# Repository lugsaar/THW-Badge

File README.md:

# THW-Badge

 [![CC BY-NC-SA 4.0][cc-by-nc-sa-shield]][cc-by-nc-sa]

## Images 

## License 

This work is licensed under a
[Creative Commons Attribution-NonCommercial-ShareAlike 4.0 International License][cc-by-nc-sa].

[![CC BY-NC-SA 4.0][cc-by-nc-sa-image]][cc-by-nc-sa]

[cc-by-nc-sa]: http://creativecommons.org/licenses/by-nc-sa/4.0/
[cc-by-nc-sa-image]: https://licensebuttons.net/l/by-nc-sa/4.0/88x31.png
[cc-by-nc-sa-shield]: https://img.shields.io/badge/License-CC%20BY--NC--SA%204.0-lightgrey.svg

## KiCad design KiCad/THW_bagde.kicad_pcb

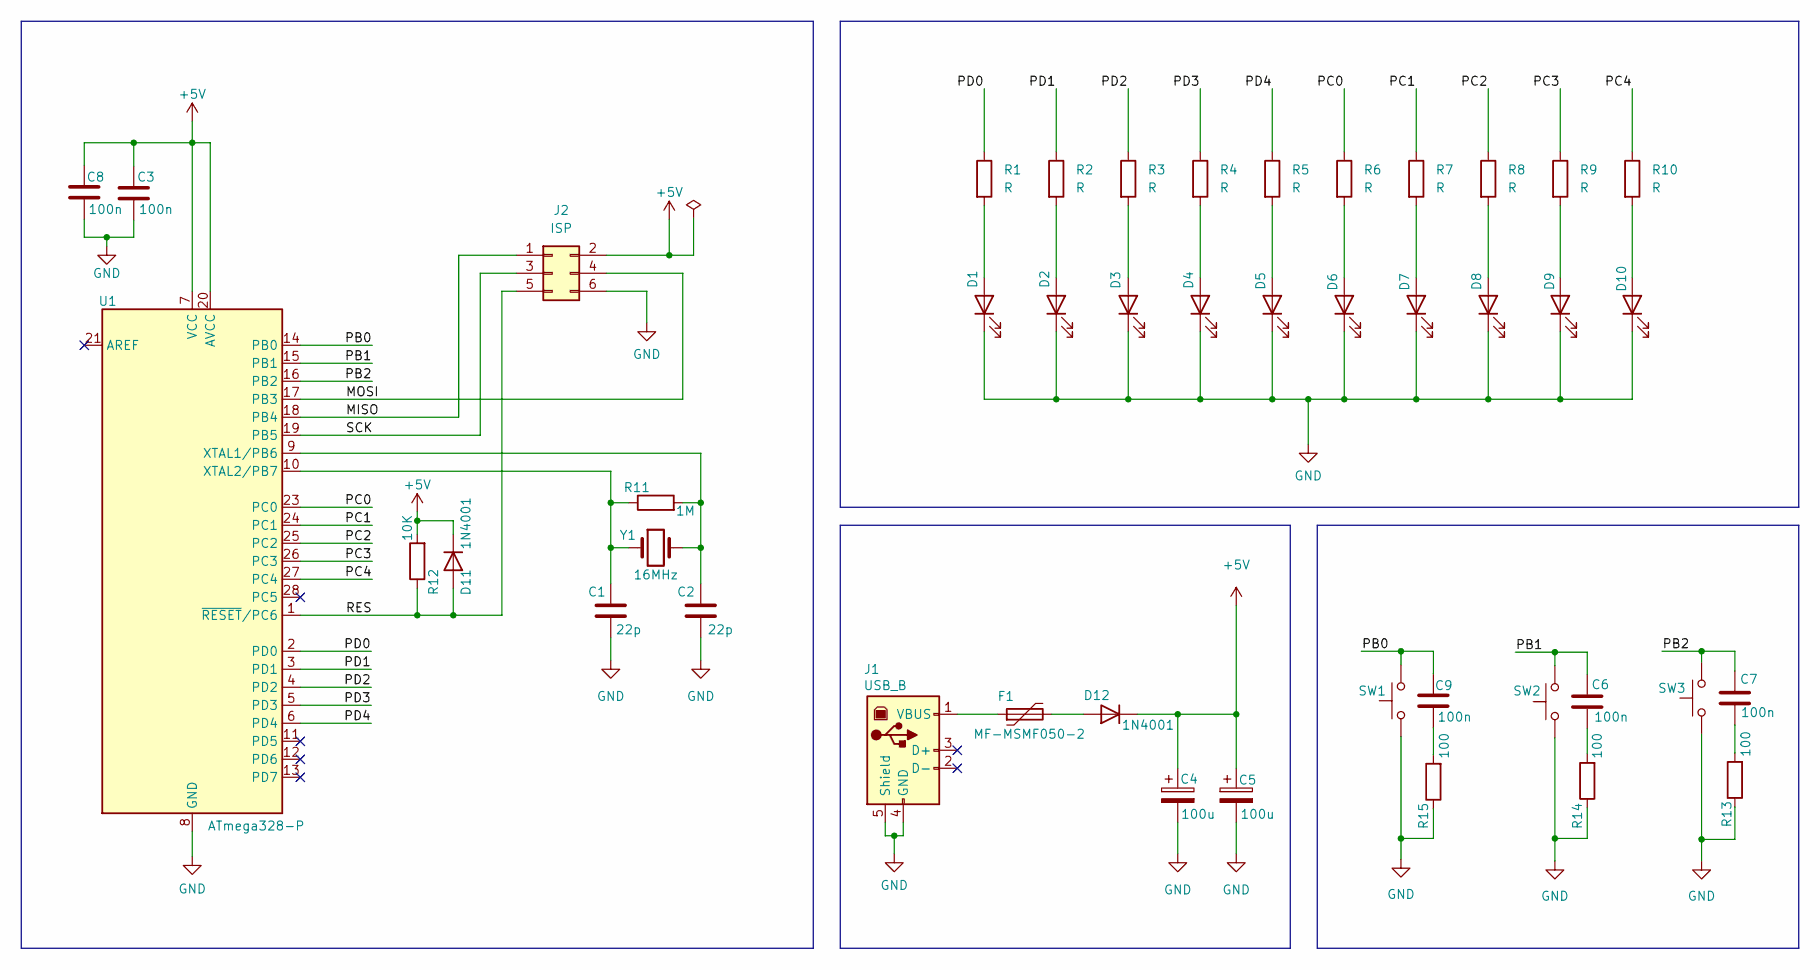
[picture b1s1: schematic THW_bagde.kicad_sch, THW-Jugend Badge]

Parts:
C1, C2: 22p; C_Disc_D3.8mm_W2.6mm_P2.50mm
C3, C6, C7, C8, C9: 100n; C_Disc_D3.8mm_W2.6mm_P2.50mm
C4, C5: 100u; CP_Radial_D6.3mm_P2.50mm
D1, D2, D3, D4, D5, D6, D7, D8, D9, D10: LED; LED_D3.0mm_Clear
D11, D12: 1N4001; D_DO-41_SOD81_P10.16mm_Horizontal
F1: MF-MSMF050-2; Fuse_1812_4532Metric
J1: USB_B; USB_B_Lumberg_2411_02_Horizontal
J2: ISP; PinHeader_2x03_P2.54mm_Vertical
R1, R2, R3, R4, R5, R6, R7, R8, R9, R10: R; R_Axial_DIN0207_L6.3mm_D2.5mm_P10.16mm_Horizontal
R11: 1M; R_Axial_DIN0207_L6.3mm_D2.5mm_P10.16mm_Horizontal
R12: 10K; R_Axial_DIN0207_L6.3mm_D2.5mm_P10.16mm_Horizontal
R13, R14, R15: 100; R_Axial_DIN0207_L6.3mm_D2.5mm_P10.16mm_Horizontal
SW1, SW2, SW3: SW_Push; SW_PUSH_6mm
U1: ATmega328-P; DIP-28_W7.62mm
Y1: 16MHz; Crystal_HC49-4H_Vertical

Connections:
+5V: C3.1, C4.1, C5.1, C8.1, D11.1 (K), D12.1 (K), J2.2, R12.2, U1.7 (VCC), U1.20 (AVCC)
/MISO: J2.1, U1.18 (PB4)
/MOSI: J2.4, U1.17 (PB3)
/PB0: C9.1, SW1.2, U1.14 (PB0)
/PB1: C6.1, SW2.2, U1.15 (PB1)
/PB2: C7.1, SW3.2, U1.16 (PB2)
/PC0: R6.1, U1.23 (PC0)
/PC1: R7.1, U1.24 (PC1)
/PC2: R8.1, U1.25 (PC2)
/PC3: R9.1, U1.26 (PC3)
/PC4: R10.1, U1.27 (PC4)
/PD0: R1.1, U1.2 (PD0)
/PD1: R2.1, U1.3 (PD1)
/PD2: R3.1, U1.4 (PD2)
/PD3: R4.1, U1.5 (PD3)
/PD4: R5.1, U1.6 (PD4)
/RES: D11.2 (A), J2.5, R12.1, U1.1 (~RESET/PC6)
/SCK: J2.3, U1.19 (PB5)
GND: C1.2, C2.2, C3.2, C4.2, C5.2, C8.2, D1.1 (K), D2.1 (K), D3.1 (K), D4.1 (K), D5.1 (K), D6.1 (K), D7.1 (K), D8.1 (K), D9.1 (K), D10.1 (K), J1.4 (GND), J1.5 (Shield), J2.6, R13.1, R14.1, R15.1, SW1.1, SW2.1, SW3.1, U1.8 (GND), U1.22 (GND)
unnamed: C1.1, R11.1, U1.10 (XTAL2/PB7), Y1.1
unnamed: C2.1, R11.2, U1.9 (XTAL1/PB6), Y1.2
unnamed: C7.2, R13.2
unnamed: C9.2, R15.2
unnamed: D1.2 (A), R1.2
unnamed: D2.2 (A), R2.2
unnamed: D3.2 (A), R3.2
unnamed: D4.2 (A), R4.2
unnamed: D5.2 (A), R5.2
unnamed: D6.2 (A), R6.2
unnamed: D7.2 (A), R7.2
unnamed: D8.2 (A), R8.2
unnamed: D9.2 (A), R9.2
unnamed: D10.2 (A), R10.2
unnamed: D12.2 (A), F1.2
unnamed: F1.1, J1.1 (VBUS)
unnamed: C6.2, R14.2

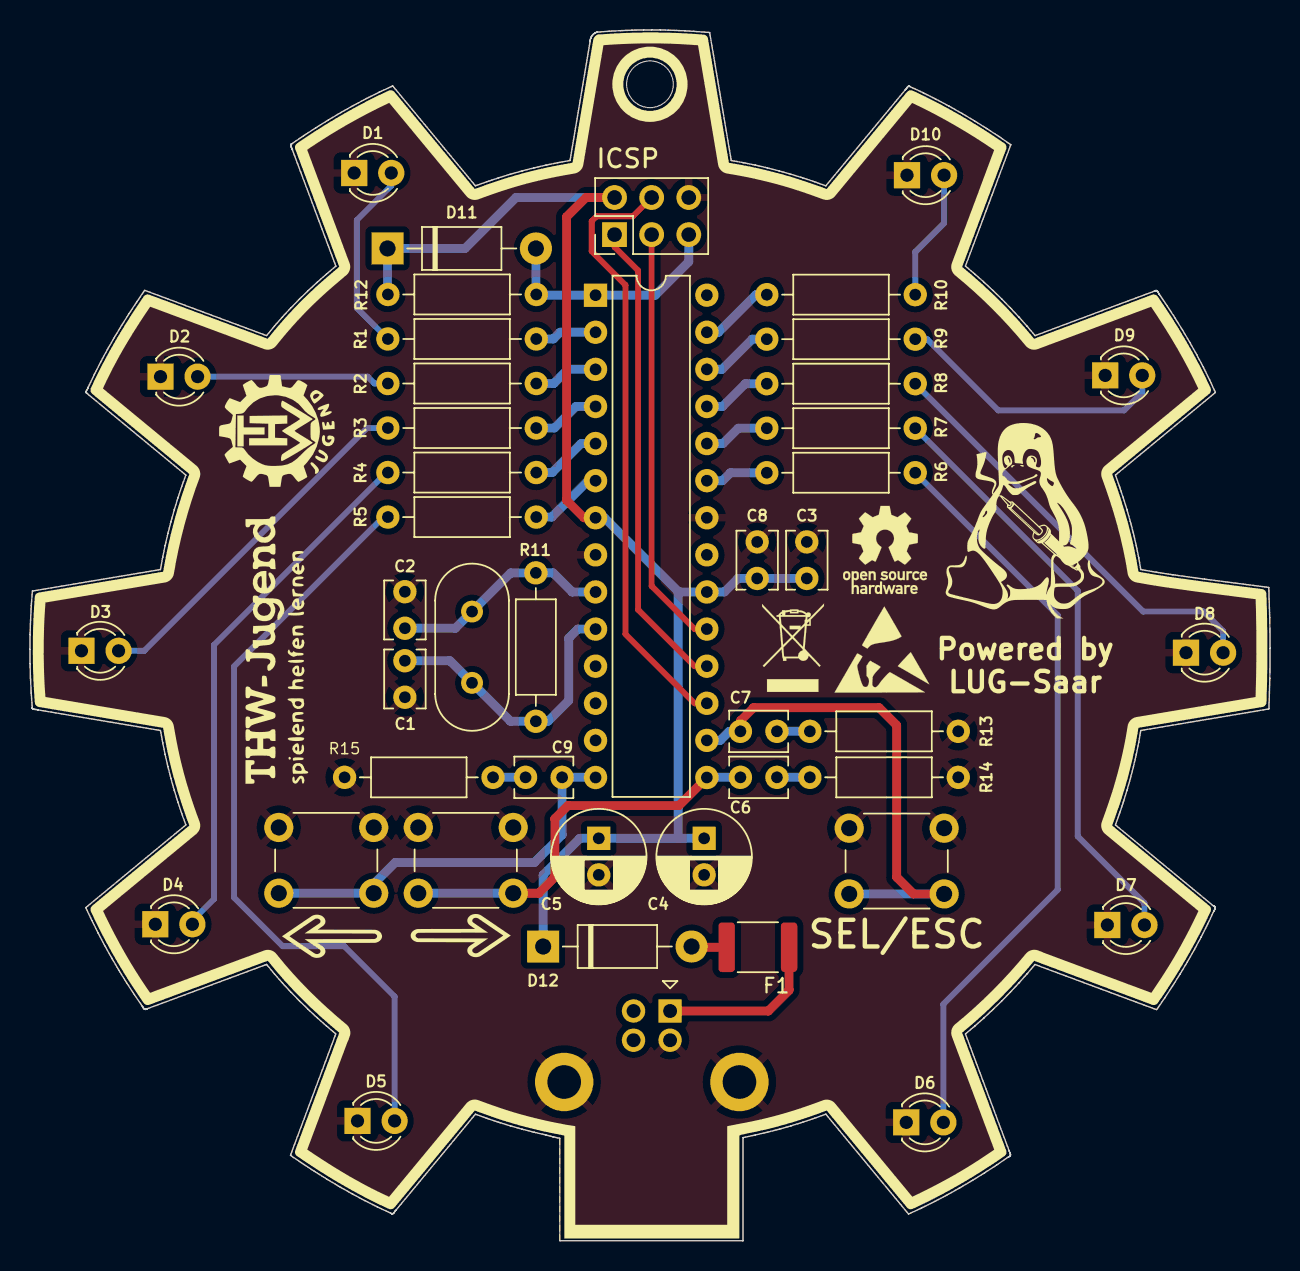
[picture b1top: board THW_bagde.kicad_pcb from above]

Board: 2 copper layers, 84.9 x 82.9 mm, 44 parts (0 on the bottom side), 36 nets.

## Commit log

2023-04-10 place some parts to see dimension of badge
2023-04-23 adding lugsaar worksheet file
2023-04-23 LED placement
2023-04-27 ICSP-Header added
2023-05-01 adding firmware for tests
2023-05-02 fixing some silkscreen issues and adding image to README file
2023-05-03 switching to plain avr lib instead arduino framework
2023-05-06 first tests with tks-badge firmware
2023-05-06 fixing pin mapping
2023-05-06 updating image for docu
2023-05-13 Changing user button circuit. Routing first components. Resize LUG logo in Drawing sheet.
2023-05-14 adding importent symbols
2023-05-25 routing LEDs
2023-05-26 adding GKW graphis to B.Silkscreen
2023-05-31 Adding Rendering of bottom and adding QR to GitHub Repo.
2023-06-12 adding new app
2023-07-01 first order
2023-07-01 move docs folder

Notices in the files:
KiCad/THW_bagde.kicad_sch:
Copyright © Linux User Group Saar e.V.
Licensed under CC-BY-NC-SA 4.0 Internation License
